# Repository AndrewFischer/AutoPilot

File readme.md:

# *AutoPilot*
*AutoPilot* is a mechanical numpad(numeric keypad) running [QMK](https://github.com/qmk/qmk_firmware) firmware.<br>

## License
[cc by-nc 4.0](LICENSE.md)

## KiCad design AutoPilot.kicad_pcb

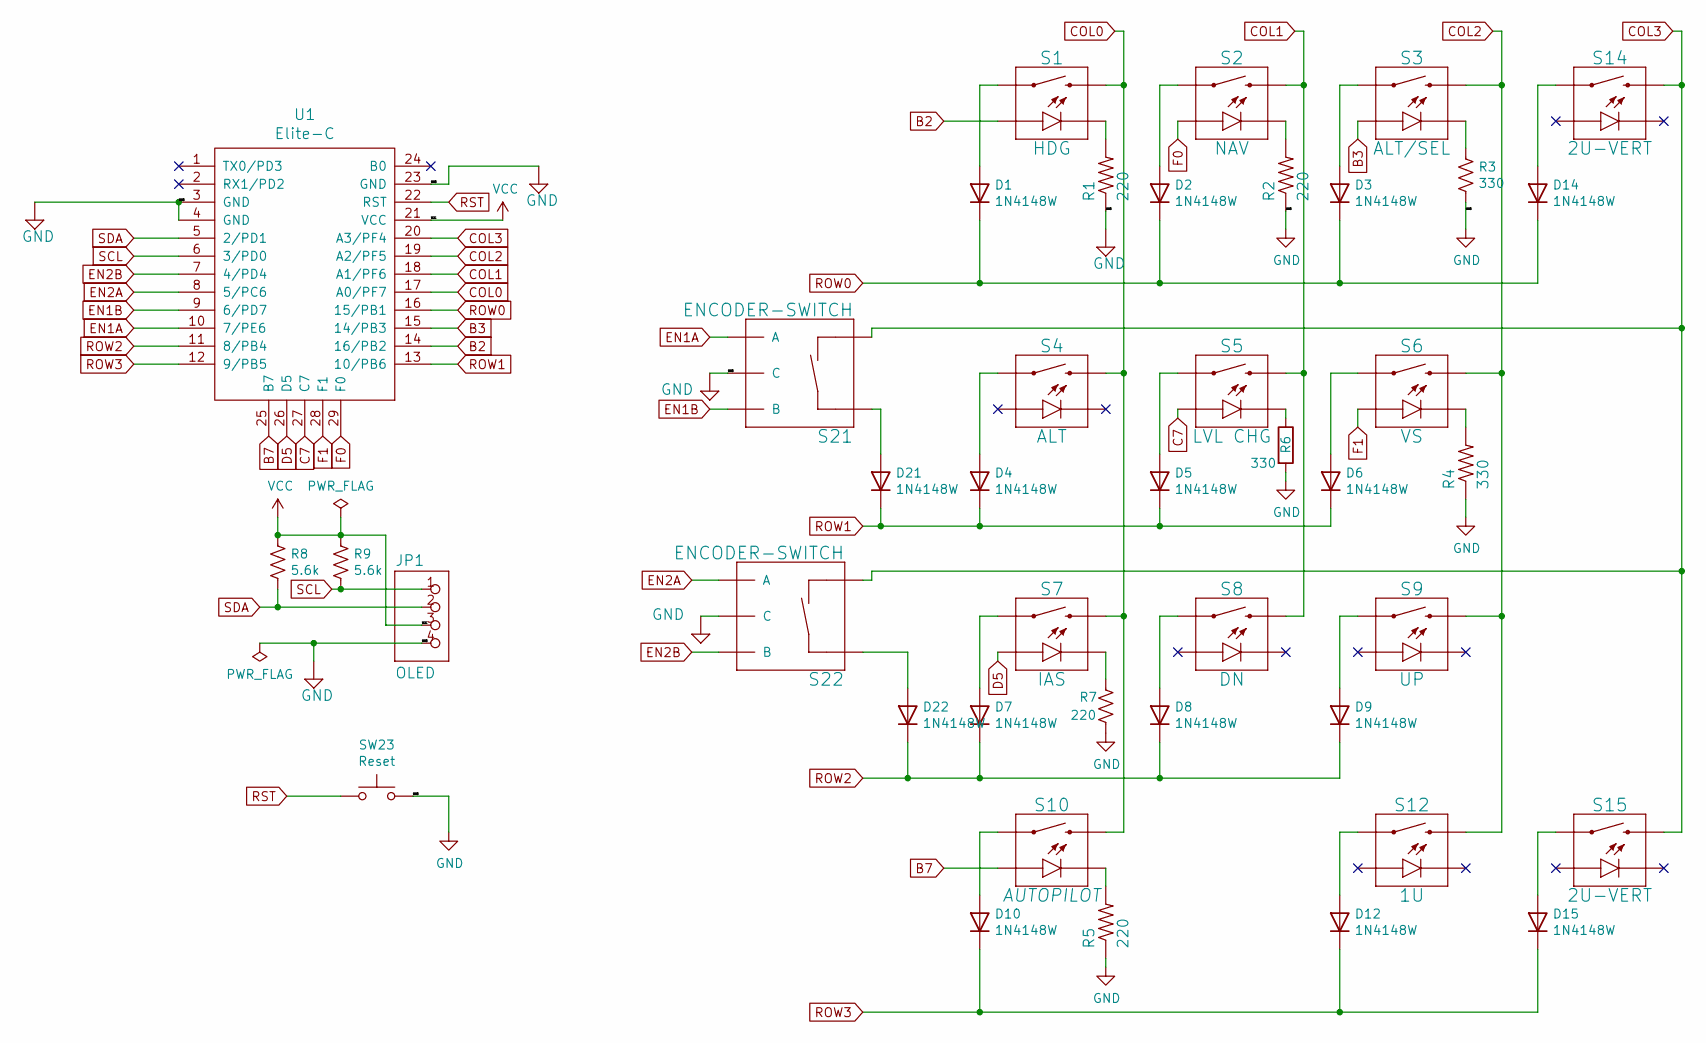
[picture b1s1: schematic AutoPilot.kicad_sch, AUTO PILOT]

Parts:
D1, D2, D3, D4, D5, D6, D7, D8, D9, D10, D12, D14, D15, D21, D22: 1N4148W; D_SOD-123; LCSC C81598
JP1: OLED; 1X04
R1, R2, R5, R7: 220; R_0805_2012Metric_Pad1.20x1.40mm_HandSolder; LCSC C17557
R3, R4: 330; R_0805_2012Metric_Pad1.20x1.40mm_HandSolder; LCSC C17630
R6: 330; R_0805_2012Metric_Pad1.20x1.40mm_HandSolder
R8, R9: 5.6k; R_0805_2012Metric; LCSC C4382
S1: HDG; CHERRY-MX-LED-1U
S2: NAV; CHERRY-MX-LED-1U
S3: ALT/SEL; CHERRY-MX-LED-1U
S4: ALT; CHERRY-MX-LED-1U
S5: LVL CHG; CHERRY-MX-LED-1U
S6: VS; CHERRY-MX-LED-1U
S7: IAS; CHERRY-MX-LED-1U
S8: DN; CHERRY-MX-LED-1U
S9: UP; CHERRY-MX-LED-1U
S10: AUTOPILOT; CHERRY-MX-LED-1X2U
S12: 1U; CHERRY-MX-LED-1U
S14, S15: 2U-VERT; CHERRY-MX-LED-2X1U
S21, S22: ENCODER-SWITCH; ROTARY_ENC_PLAIN
SW23: Reset; SW_PUSH_6mm_H5mm
U1: Elite-C; Elite-C-castellated-29pin-holes

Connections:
B2: S1.A, U1.14 (16/PB2)
B3: S3.A, U1.15 (14/PB3)
B7: S10.A, U1.25 (B7)
C7: S5.A, U1.27 (C7)
COL0: S1.S2 (2), S4.S2 (2), S7.S2 (2), S10.S2 (2), U1.17 (A0/PF7)
COL1: S2.S2 (2), S5.S2 (2), S8.S2 (2), U1.18 (A1/PF6)
COL2: S3.S2 (2), S6.S2 (2), S9.S2 (2), S12.S2 (2), U1.19 (A2/PF5)
COL3: S14.S2 (2), S15.S2 (2), S21.SW-, S22.SW-, U1.20 (A3/PF4)
D5: S7.A, U1.26 (D5)
EN1A: S21.A, U1.10 (7/PE6)
EN1B: S21.B, U1.9 (6/PD7)
EN2A: S22.A, U1.8 (5/PC6)
EN2B: S22.B, U1.7 (4/PD4)
F0: S2.A, U1.29 (F0)
F1: S6.A, U1.28 (F1)
GND: JP1.4, R1.1, R2.1, R3.2, R4.1, R5.1, R6.2, R7.2, S21.C, S22.C, SW23.2, U1.3 (GND), U1.4 (GND), U1.23 (GND)
unnamed: D1.2 (A), S1.S1 (1)
unnamed: D2.2 (A), S2.S1 (1)
unnamed: D3.2 (A), S3.S1 (1)
unnamed: D4.2 (A), S4.S1 (1)
unnamed: D5.2 (A), S5.S1 (1)
unnamed: D6.2 (A), S6.S1 (1)
unnamed: D7.2 (A), S7.S1 (1)
unnamed: D8.2 (A), S8.S1 (1)
unnamed: D9.2 (A), S9.S1 (1)
unnamed: D10.2 (A), S10.S1 (1)
unnamed: D12.2 (A), S12.S1 (1)
unnamed: D14.2 (A), S14.S1 (1)
unnamed: D15.2 (A), S15.S1 (1)
unnamed: D21.2 (A), S21.SW+
unnamed: D22.2 (A), S22.SW+
unnamed: R1.2, S1.K (C)
unnamed: R2.2, S2.K (C)
unnamed: R3.1, S3.K (C)
unnamed: R4.2, S6.K (C)
unnamed: R5.2, S10.K (C)
unnamed: R6.1, S5.K (C)
unnamed: R7.1, S7.K (C)
ROW0: D1.1 (K), D2.1 (K), D3.1 (K), D14.1 (K), U1.16 (15/PB1)
ROW1: D4.1 (K), D5.1 (K), D6.1 (K), D21.1 (K), U1.13 (10/PB6)
ROW2: D7.1 (K), D8.1 (K), D9.1 (K), D22.1 (K), U1.11 (8/PB4)
ROW3: D10.1 (K), D12.1 (K), D15.1 (K), U1.12 (9/PB5)
RST: SW23.1, U1.22 (RST)
SCL: JP1.1, R9.2, U1.6 (3/PD0)
SDA: JP1.2, R8.2, U1.5 (2/PD1)
VCC: JP1.3, R8.1, R9.1, U1.21 (VCC)

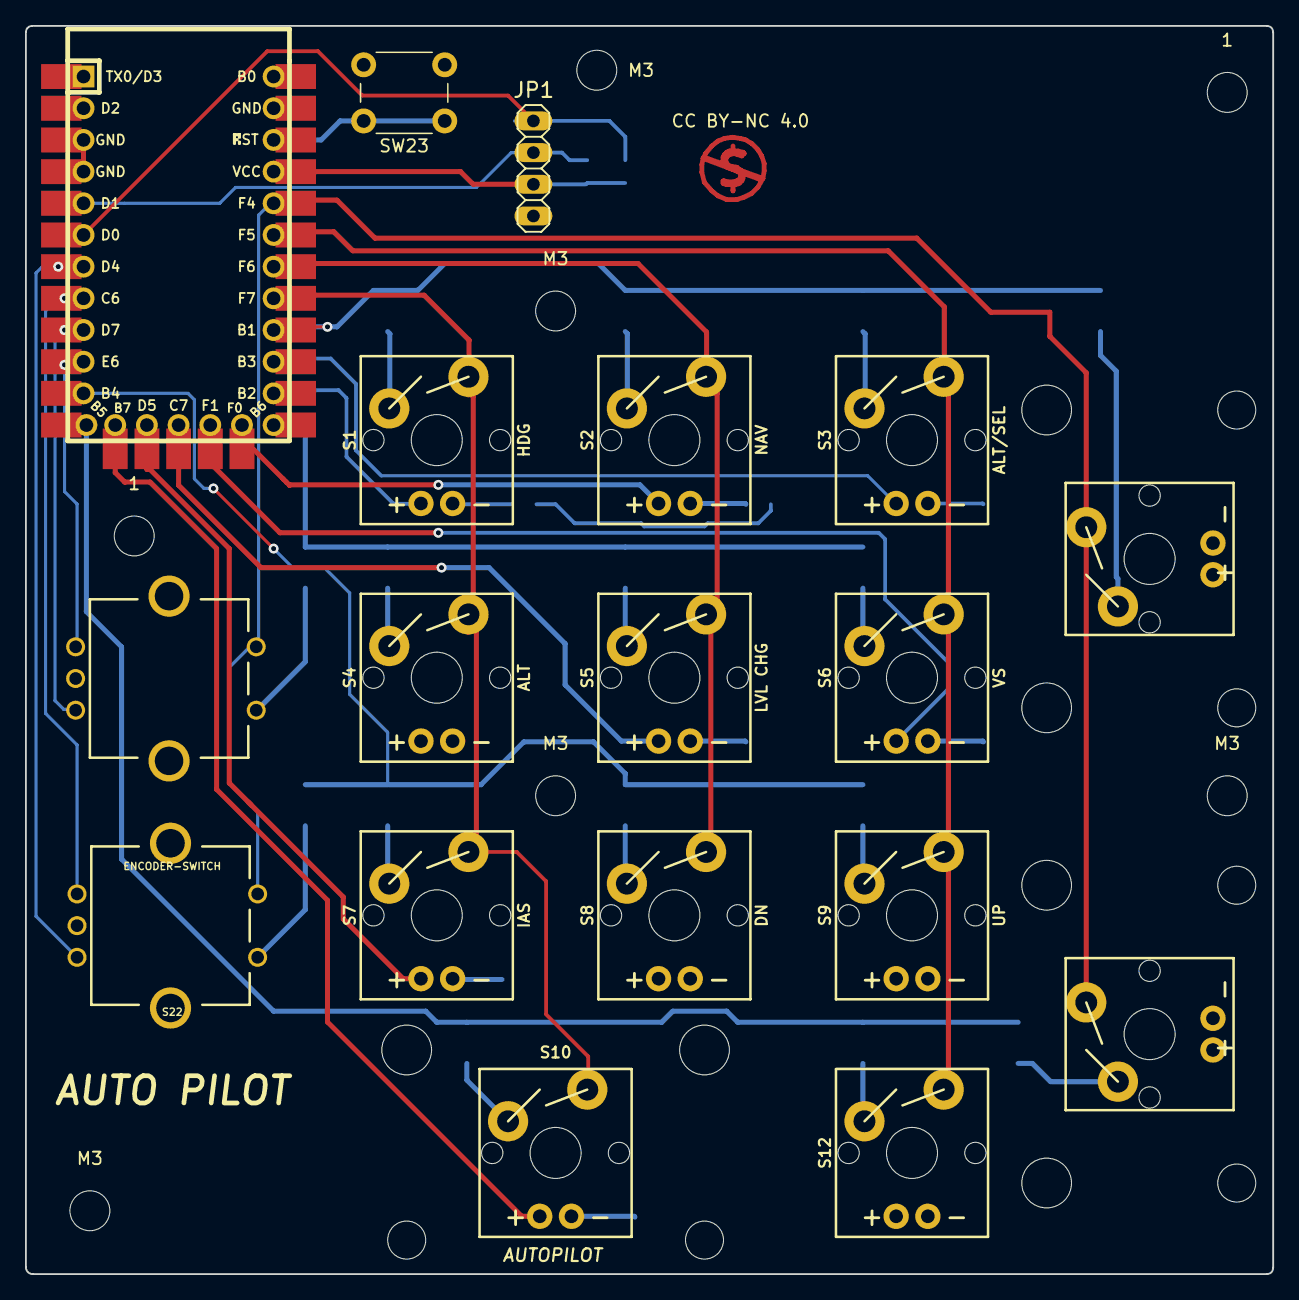
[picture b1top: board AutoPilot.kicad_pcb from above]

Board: 2 copper layers, 100.0 x 100.1 mm, 50 parts (0 on the bottom side), 46 nets.

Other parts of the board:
1, 1#2: M3; MountingHole_3.2mm_M3
CC BY-NC 4.0: CC-Noncommercial; Symbol_CC-Noncommercial_CopperTop_Small
M3, M3#2, M3#3, M3#4, M3#5: M3; MountingHole_3.2mm_M3

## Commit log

2023-03-29 initial entry
2023-03-29 add license
2023-03-29 Fix typos
    Fix Typos

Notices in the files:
AutoPilot.kicad_pcb:
Copyright (c) 2021 Andrew Fischer
AutoPilot.kicad_sch:
creativecommons.org/licenses/by-nc/4.0
© Andrew Fischer 2021
